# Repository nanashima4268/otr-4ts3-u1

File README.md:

# OTR-4TS3-U1

Open Tuner Receiver。地デジ、BS/110 度 CS、CATV を 4 系統同時に受信できるボードで、ISDB-S3（BS4K）の復調チップへの載せ替えにも対応する。

- ホストとの接続：USB3（FX3）。FPGA（iCE40HX4K-TQ144、中身は HX8K と同じダイ）で 4 系統の TS／TLV を 1 本にまとめる
- 形状：PCIe ロープロファイル（PCIe からは電源だけを取る）と外付け箱の両対応
- 暗号の解除（B-CAS、ACAS）の機能は持たない
- ライセンス（`LICENSES/` を参照）
  - `hw/`：CERN-OHL-S-2.0
  - `fpga/` と `host/`：GPL-2.0-only（px4_drv から派生したコードを含むため）
  - `fx3/`：MIT（FX3 SDK のライブラリはソース非公開のため。ファームのバイナリには Cypress の利用規約がかかる）
  - `docs/`：CERN-OHL-S-2.0（ハードウェア設計資料の一部として）

## ドキュメント

- [docs/research.md](docs/research.md)：事前調査（参照ボードの解析、チップ、先行例、RF・電源・製造の定石、法的な線引き、リスク）
- [docs/decisions.md](docs/decisions.md)：決定事項ログ
- [docs/architecture.md](docs/architecture.md)：ブロック図、電源ツリー、電力見積もり
- [docs/measurement-procedure.md](docs/measurement-procedure.md)：参照ボードの実測手順
- [docs/bom-candidates.md](docs/bom-candidates.md)：部品候補表
- [docs/preverification-plan.md](docs/preverification-plan.md)：ファームウェアとソフトウェアの先行検証計画
- [docs/reference/photos/](docs/reference/photos/)：参照ボード DTV02A-4TS-P の写真

## 状態

設計前の調査段階。回路図はまだない。参照ボードの実測（docs/measurement-procedure.md）を進めている。

## 注意

- 本プロジェクトは、B-CAS や ACAS で暗号化された放送を復号する機能を提供しない。また、提供する予定もない。
- Sony の CXD2856ER と CXD2858ER の情報は、公開されている GPL のドライバと、購入した製品の実測から得たもの。Sony とは関係がなく、NDA に基づく情報は含まない。

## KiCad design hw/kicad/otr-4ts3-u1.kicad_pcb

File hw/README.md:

# hw

KiCad project for the OTR-4TS3-U1 board (4-layer, JLC04161H-7628 stackup). License: CERN-OHL-S-2.0 (see ../LICENSES).
See ../docs/architecture.md.

## Generated design (D-51)

The schematic is generated, not drawn: `hw/gen/design.py` describes the circuit in Python, and `hw/gen/schgen.py` writes `hw/kicad/*.kicad_sch`. Every pin connects through a global label at its end point, so the netlist is exactly the description.

```sh
python3 hw/gen/symbols.py   # project symbols -> hw/lib/otr.kicad_sym (FX3 from the datasheet ball map)
python3 hw/gen/design.py    # schematic + verification
```

Verification:
- The netlist that KiCad exports (`kicad-cli sch export netlist`) must equal the description.
- Every pin of every symbol must be assigned (`NC` for unused pins).
- Pins that the library draws stacked must share a net.
- Library no-connect pins must be `NC`.
- ERC runs (`kicad-cli sch erc`).

Phase 1 covers everything except the Sony receiver core. The receiver core waits for the reference-board measurement and the photo survey, because the CXD2856ER/CXD2858ER pinouts are not public.

Status (2026-11-01):
- Sheets done:
  - FX3
  - FPGA (also generates `fpga/syn/otr_top.pcf`)
  - Power: PCIe/DC 12 V OR, TPS54302 3.3 V, LDOs, `+VIO_TS` selection
  - USB: Type-C via HD3SS3220, or the internal header
  - Control: TCA9546A, LNA bypass inverter
  - RF front end: F jacks, LNA with bypass, 4-way splitters
- The netlist equals the description, and ERC reports 0 errors.
- The 32 remaining ERC warnings are labels for the receiver interface: TS*, RF_T*/RF_S*, CH*_PWR_EN/RST_N. They wait for the receiver sheet (Sony parts, after the measurement).
- Project symbols and footprints are generated by `hw/gen/symbols.py`:
  - CYUSB3014 from the ball map
  - HD3SS3220
  - The DS803FPR0016 F-jack footprint from the maker's recommended layout

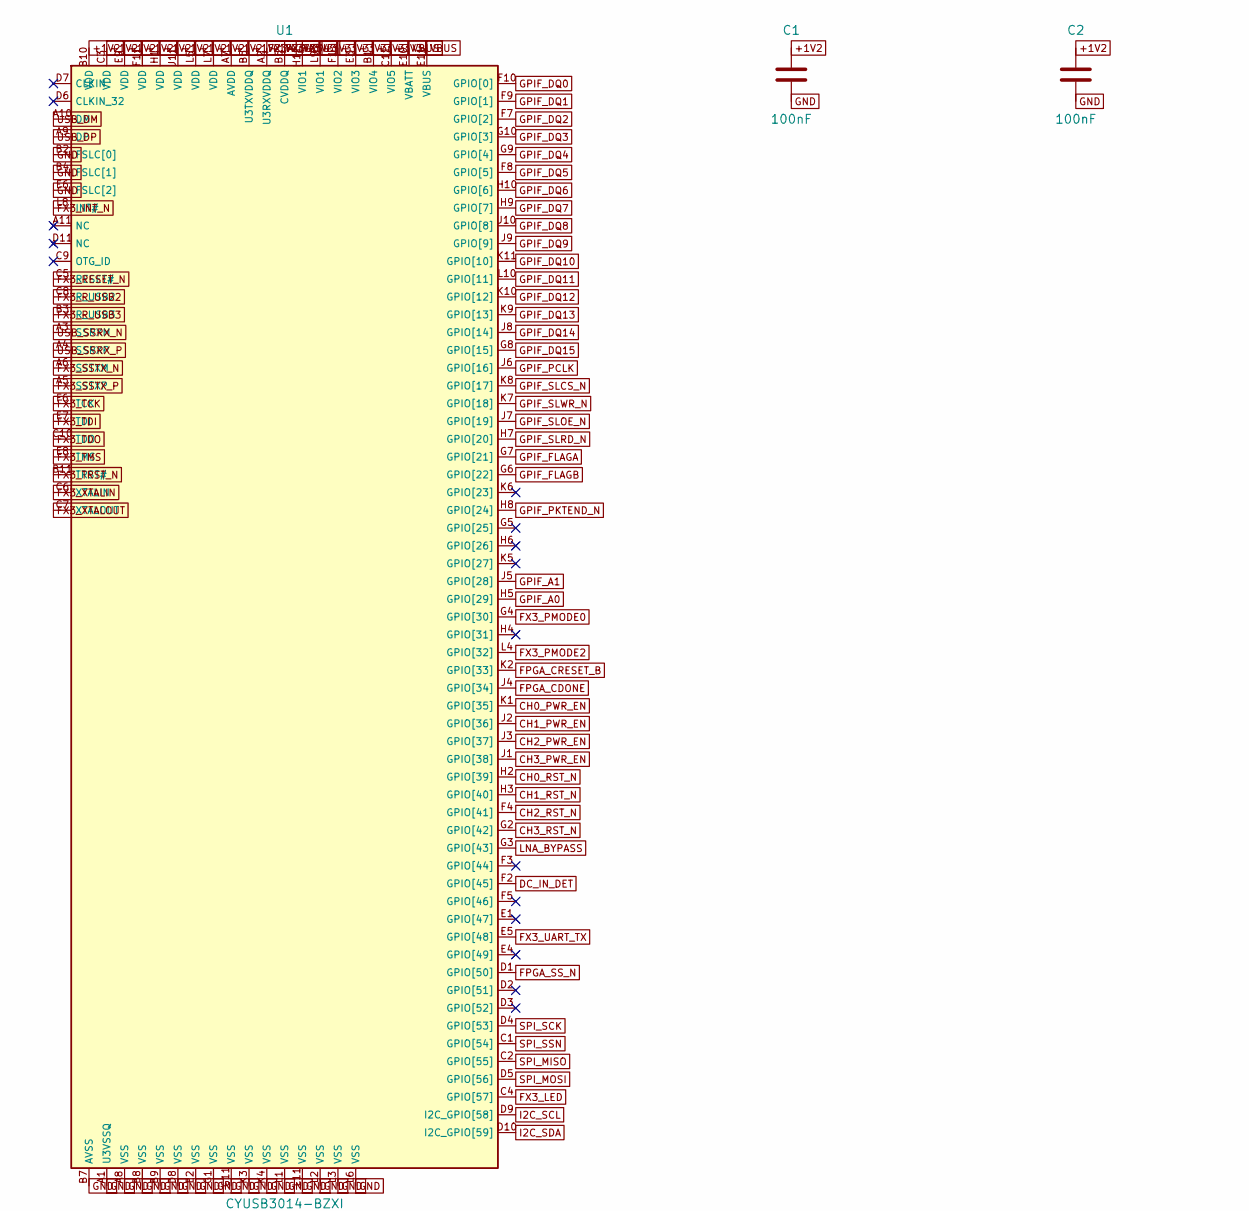
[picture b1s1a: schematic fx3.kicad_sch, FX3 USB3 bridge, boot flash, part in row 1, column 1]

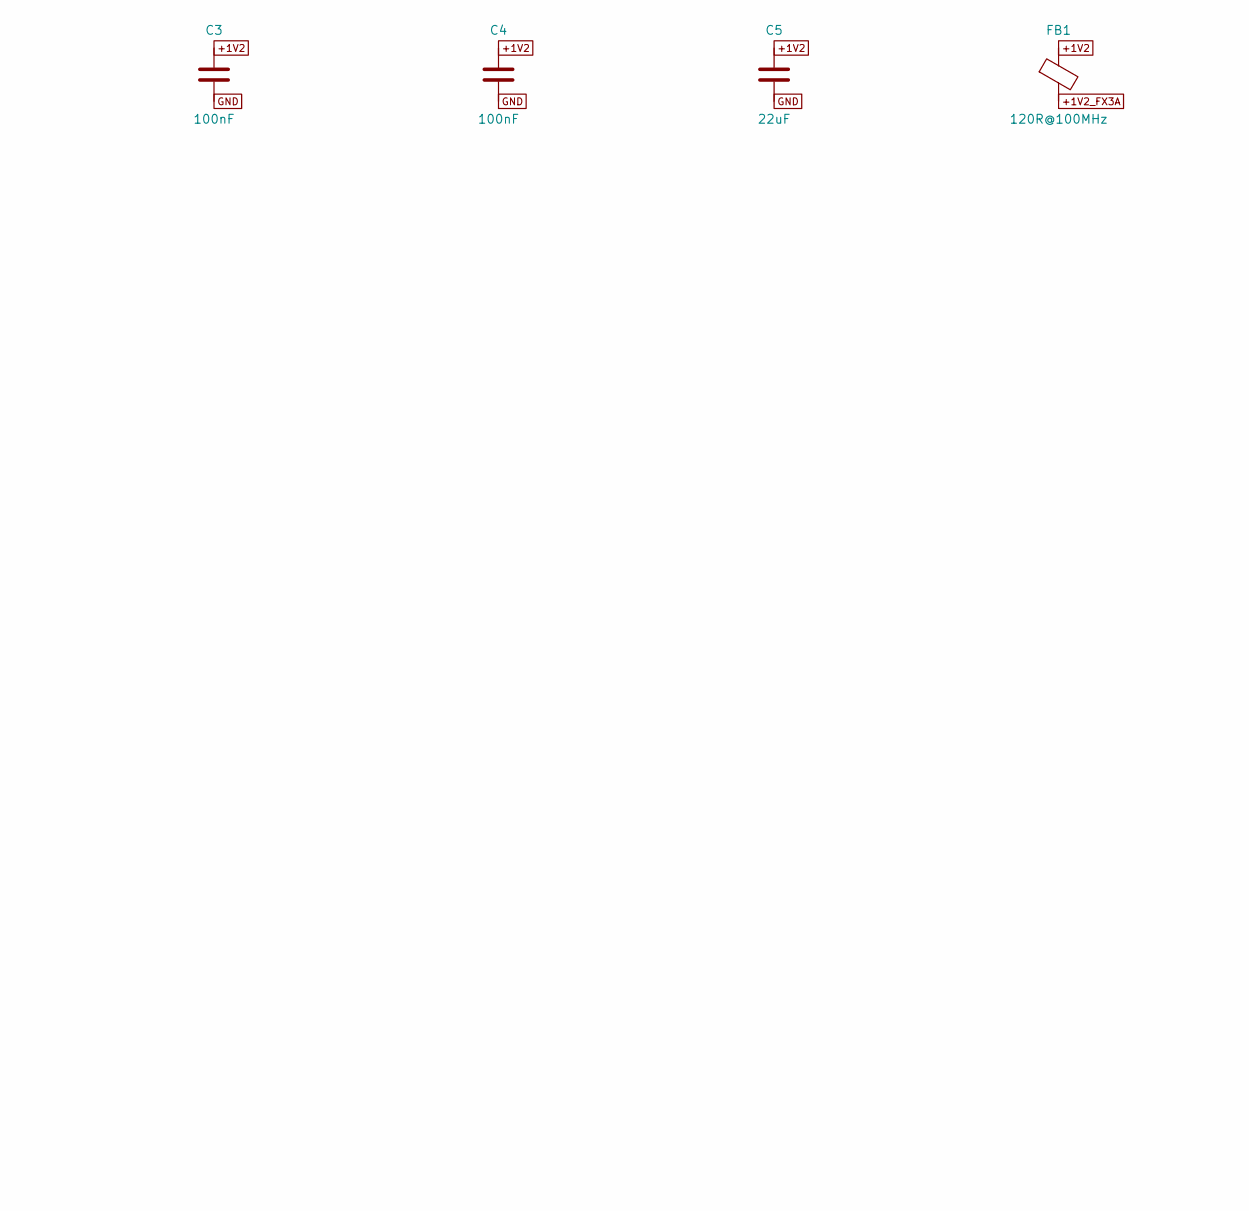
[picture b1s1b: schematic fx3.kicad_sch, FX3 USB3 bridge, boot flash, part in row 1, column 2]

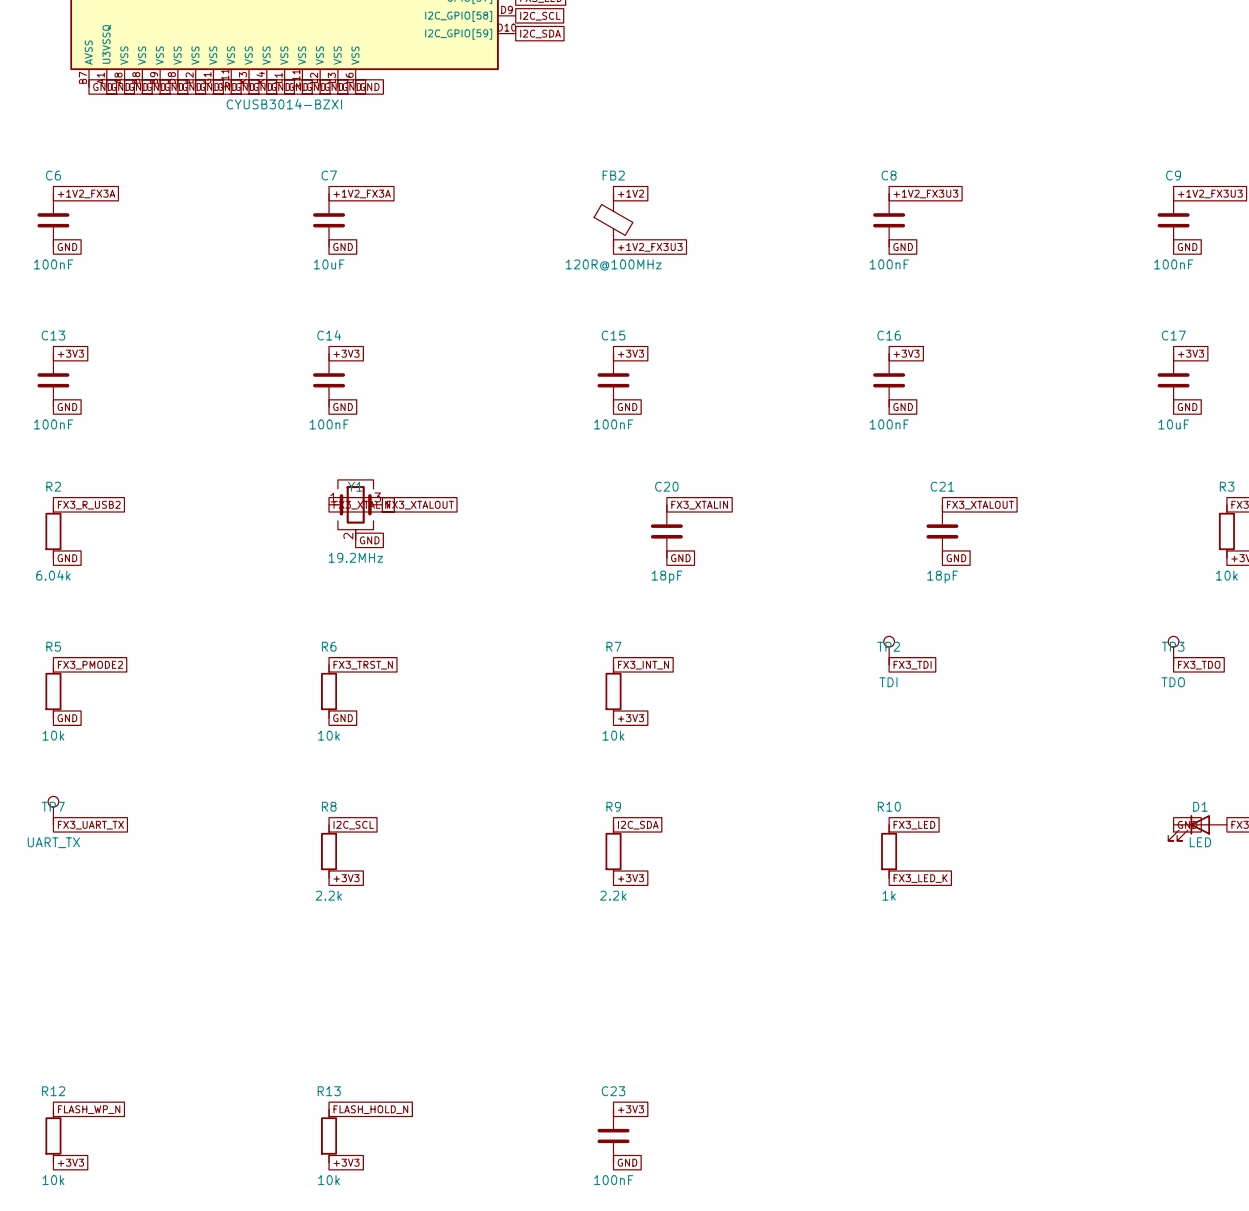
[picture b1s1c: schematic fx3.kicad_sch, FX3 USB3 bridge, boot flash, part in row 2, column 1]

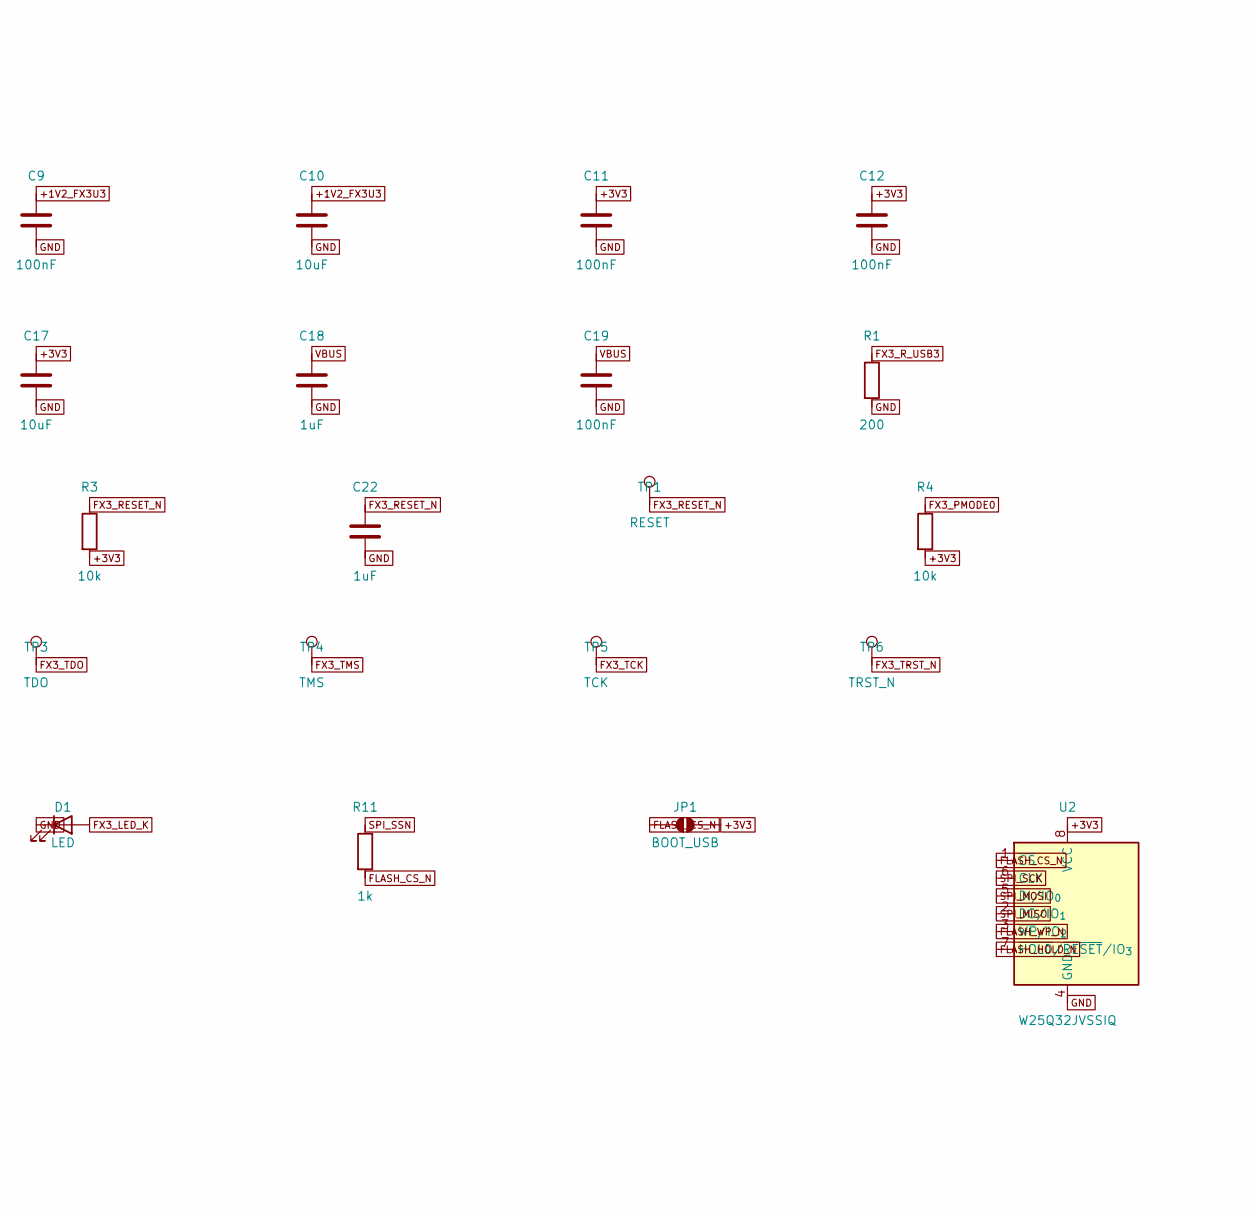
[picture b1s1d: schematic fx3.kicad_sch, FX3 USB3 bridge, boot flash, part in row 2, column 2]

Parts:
C1, C2, C3, C4, C6, C8, C9, C11, C12, C13, C14, C15, C16, C19, C23: 100nF; C_0402_1005Metric; LCSC C1525
C5: 22uF; C_0805_2012Metric; LCSC C45783
C7, C10, C17: 10uF; C_0603_1608Metric; LCSC C19702
C18, C22: 1uF; C_0402_1005Metric; LCSC C52923
C20, C21: 18pF; C_0402_1005Metric; LCSC C1549
D1: LED; LED_0603_1608Metric; LCSC C2286
FB1, FB2: 120R@100MHz; L_0603_1608Metric; LCSC C14709
JP1: BOOT_USB; SolderJumper-2_P1.3mm_Open_RoundedPad1.0x1.5mm
R1: 200; R_0402_1005Metric; LCSC C25087
R2: 6.04k; R_0402_1005Metric; LCSC C97819
R3, R4, R5, R6, R7, R12, R13: 10k; R_0402_1005Metric; LCSC C25744
R8, R9: 2.2k; R_0402_1005Metric; LCSC C25879
R10, R11: 1k; R_0402_1005Metric; LCSC C11702
TP1: RESET; TestPoint_Pad_D1.0mm
TP2: TDI; TestPoint_Pad_D1.0mm
TP3: TDO; TestPoint_Pad_D1.0mm
TP4: TMS; TestPoint_Pad_D1.0mm
TP5: TCK; TestPoint_Pad_D1.0mm
TP6: TRST_N; TestPoint_Pad_D1.0mm
TP7: UART_TX; TestPoint_Pad_D1.0mm
U1: CYUSB3014-BZXI; TFBGA-121_10x10mm_Layout11x11_P0.8mm; LCSC C57294
U2: W25Q32JVSSIQ; SOIC-8_5.3x5.3mm_P1.27mm; LCSC C179173
Y1: 19.2MHz; Crystal_SMD_3225-4Pin_3.2x2.5mm; LCSC C358650

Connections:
+1V2: C1.1, C2.1, C3.1, C4.1, C5.1, FB1.1, FB2.1, U1.B10 (VDD), U1.C3 (VDD), U1.E9 (VDD), U1.F11 (VDD), U1.H1 (VDD), U1.J11 (VDD), U1.L5 (VDD), U1.L7 (VDD); also elsewhere on the board
+1V2_FX3A: C6.1, C7.1, FB1.2, U1.A7 (AVDD)
+1V2_FX3U3: C8.1, C9.1, C10.1, FB2.2, U1.A2 (U3RXVDDQ), U1.B5 (U3TXVDDQ)
+3V3: C11.1, C12.1, C13.1, C14.1, C15.1, C16.1, C17.1, C23.1, JP1.2 (B), R3.2, R4.2, R7.2, R8.2, R9.2, R12.2, R13.2, U1.B1 (VIO4), U1.B6 (CVDDQ), U1.C11 (VIO5), U1.E3 (VIO3), U1.F1 (VIO2), U1.H11 (VIO1), U1.L9 (VIO1), U2.8 (VCC); also elsewhere on the board
CH0_PWR_EN: U1.K1 (GPIO[35])
CH0_RST_N: U1.H2 (GPIO[39])
CH1_PWR_EN: U1.J2 (GPIO[36])
CH1_RST_N: U1.H3 (GPIO[40])
CH2_PWR_EN: U1.J3 (GPIO[37])
CH2_RST_N: U1.F4 (GPIO[41])
CH3_PWR_EN: U1.J1 (GPIO[38])
CH3_RST_N: U1.G2 (GPIO[42])
DC_IN_DET: U1.F2 (GPIO[45]); also elsewhere on the board
FLASH_CS_N: JP1.1 (A), R11.2, U2.1 (~CS)
FLASH_HOLD_N: R13.1, U2.7 (~HOLD/~RESET/IO_{3})
FLASH_WP_N: R12.1, U2.3 (~WP/IO_{2})
FPGA_CDONE: U1.J4 (GPIO[34]); also elsewhere on the board
FPGA_CRESET_B: U1.K2 (GPIO[33]); also elsewhere on the board
FPGA_SS_N: U1.D1 (GPIO[50]); also elsewhere on the board
FX3_INT_N: R7.1, U1.L8 (INT#)
FX3_LED: R10.1, U1.C4 (GPIO[57])
FX3_LED_K: D1.2 (A), R10.2
FX3_PMODE0: R4.1, U1.G4 (GPIO[30])
FX3_PMODE2: R5.1, U1.L4 (GPIO[32])
FX3_RESET_N: C22.1, R3.1, TP1.1, U1.C5 (RESET#)
FX3_R_USB2: R2.1, U1.C8 (R_USB2)
FX3_R_USB3: R1.1, U1.B3 (R_USB3)
FX3_SSTX_N: U1.A6 (SSTXM); also elsewhere on the board
FX3_SSTX_P: U1.A5 (SSTXP); also elsewhere on the board
FX3_TCK: TP5.1, U1.F6 (TCK)
FX3_TDI: TP2.1, U1.E7 (TDI)
FX3_TDO: TP3.1, U1.C10 (TDO)
FX3_TMS: TP4.1, U1.E8 (TMS)
FX3_TRST_N: R6.1, TP6.1, U1.B11 (TRST#)
FX3_UART_TX: TP7.1, U1.E5 (GPIO[48])
FX3_XTALIN: C20.1, U1.C6 (XTALIN), Y1.1
FX3_XTALOUT: C21.1, U1.C7 (XTALOUT), Y1.3
GND: C1.2, C2.2, C3.2, C4.2, C5.2, C6.2, C7.2, C8.2, C9.2, C10.2, C11.2, C12.2, C13.2, C14.2, C15.2, C16.2, C17.2, C18.2, C19.2, C20.2, C21.2, C22.2, C23.2, D1.1 (K), R1.2, R2.2, R5.2, R6.2, U1.A1 (U3VSSQ), U1.A8 (VSS), U1.B2 (FSLC[0]), U1.B4 (FSLC[1]), U1.B7 (AVSS), U1.B8 (VSS), U1.B9 (VSS), U1.D8 (VSS), U1.E2 (VSS), U1.E6 (FSLC[2]), U1.G1 (VSS), U1.G11 (VSS), U1.K3 (VSS), U1.K4 (VSS), U1.L1 (VSS), U1.L2 (VSS), U1.L3 (VSS), U1.L6 (VSS), U1.L11 (VSS), U2.4 (GND), Y1.2 (G), Y1.4 (G); also elsewhere on the board
GPIF_A0: U1.H5 (GPIO[29]); also elsewhere on the board
GPIF_A1: U1.J5 (GPIO[28]); also elsewhere on the board
GPIF_DQ0: U1.F10 (GPIO[0]); also elsewhere on the board
GPIF_DQ1: U1.F9 (GPIO[1]); also elsewhere on the board
GPIF_DQ2: U1.F7 (GPIO[2]); also elsewhere on the board
GPIF_DQ3: U1.G10 (GPIO[3]); also elsewhere on the board
GPIF_DQ4: U1.G9 (GPIO[4]); also elsewhere on the board
GPIF_DQ5: U1.F8 (GPIO[5]); also elsewhere on the board
GPIF_DQ6: U1.H10 (GPIO[6]); also elsewhere on the board
GPIF_DQ7: U1.H9 (GPIO[7]); also elsewhere on the board
GPIF_DQ8: U1.J10 (GPIO[8]); also elsewhere on the board
GPIF_DQ9: U1.J9 (GPIO[9]); also elsewhere on the board
GPIF_DQ10: U1.K11 (GPIO[10]); also elsewhere on the board
GPIF_DQ11: U1.L10 (GPIO[11]); also elsewhere on the board
GPIF_DQ12: U1.K10 (GPIO[12]); also elsewhere on the board
GPIF_DQ13: U1.K9 (GPIO[13]); also elsewhere on the board
GPIF_DQ14: U1.J8 (GPIO[14]); also elsewhere on the board
GPIF_DQ15: U1.G8 (GPIO[15]); also elsewhere on the board
GPIF_FLAGA: U1.G7 (GPIO[21]); also elsewhere on the board
GPIF_FLAGB: U1.G6 (GPIO[22]); also elsewhere on the board
GPIF_PCLK: U1.J6 (GPIO[16]); also elsewhere on the board
GPIF_PKTEND_N: U1.H8 (GPIO[24]); also elsewhere on the board
GPIF_SLCS_N: U1.K8 (GPIO[17]); also elsewhere on the board
GPIF_SLOE_N: U1.J7 (GPIO[19]); also elsewhere on the board
GPIF_SLRD_N: U1.H7 (GPIO[20]); also elsewhere on the board
GPIF_SLWR_N: U1.K7 (GPIO[18]); also elsewhere on the board
I2C_SCL: R8.1, U1.D9 (I2C_GPIO[58]); also elsewhere on the board
I2C_SDA: R9.1, U1.D10 (I2C_GPIO[59]); also elsewhere on the board
LNA_BYPASS: U1.G3 (GPIO[43]); also elsewhere on the board
SPI_MISO: U1.C2 (GPIO[55]), U2.2 (DO/IO_{1}); also elsewhere on the board
SPI_MOSI: U1.D5 (GPIO[56]), U2.5 (DI/IO_{0}); also elsewhere on the board
SPI_SCK: U1.D4 (GPIO[53]), U2.6 (CLK); also elsewhere on the board
SPI_SSN: R11.1, U1.C1 (GPIO[54])
USB_DM: U1.A10 (DM); also elsewhere on the board
USB_DP: U1.A9 (DP); also elsewhere on the board
USB_SSRX_N: U1.A3 (SSRXM); also elsewhere on the board
USB_SSRX_P: U1.A4 (SSRXP); also elsewhere on the board
VBUS: C18.1, C19.1, U1.E10 (VBATT), U1.E11 (VBUS); also elsewhere on the board

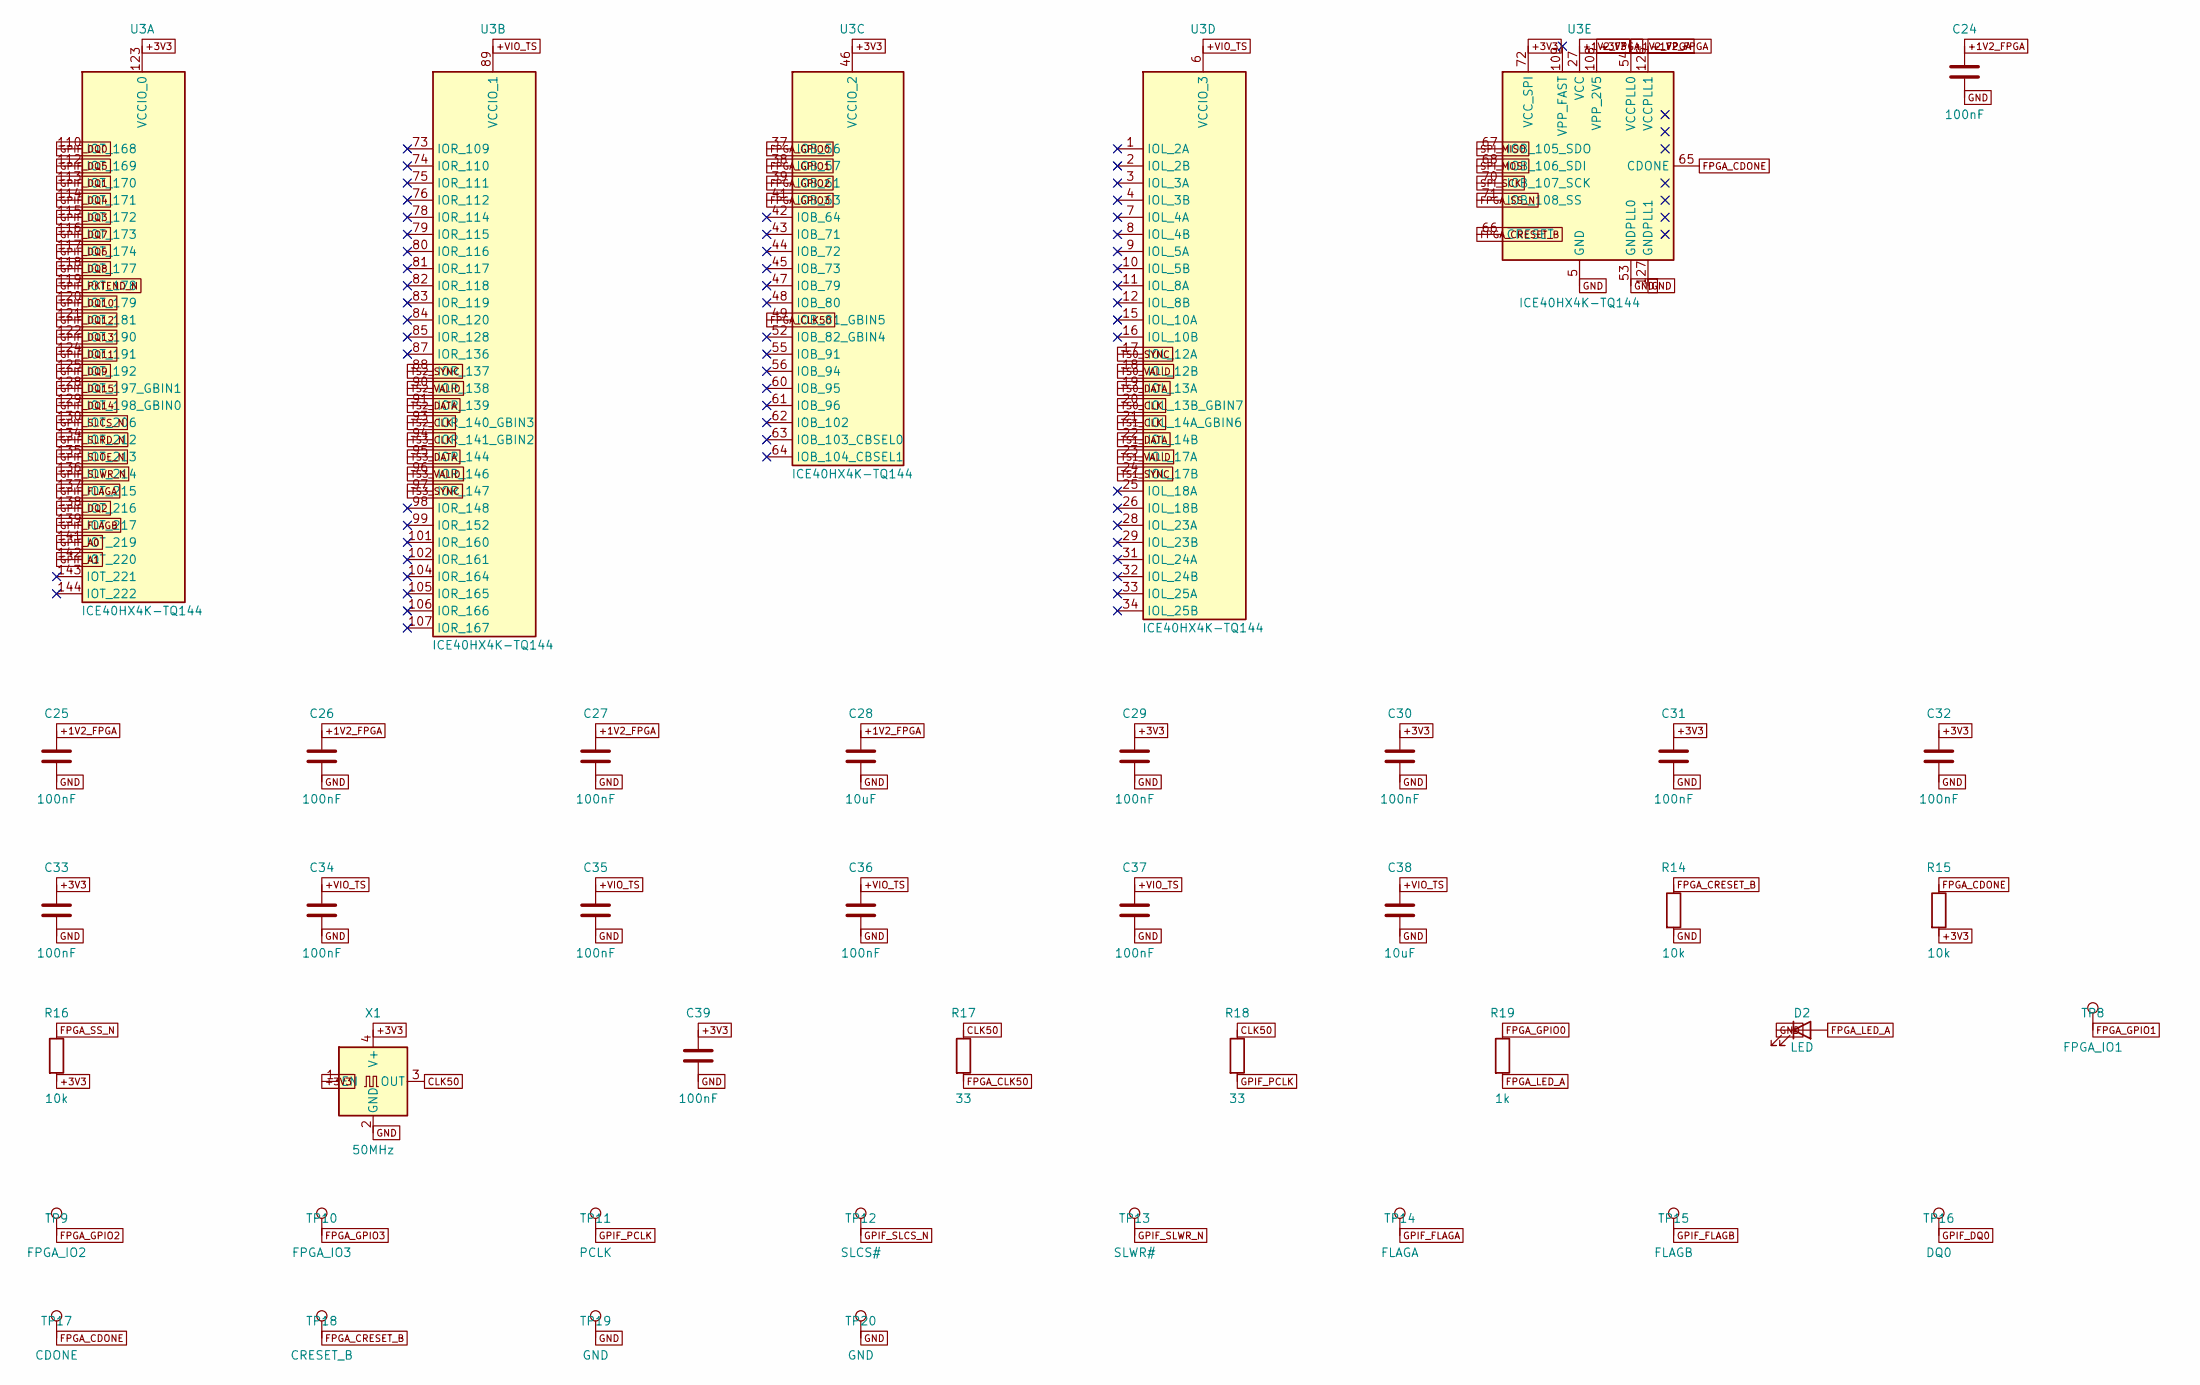
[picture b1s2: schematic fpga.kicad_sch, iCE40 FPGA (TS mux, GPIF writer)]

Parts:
C24, C25, C26, C27, C29, C30, C31, C32, C33, C34, C35, C36, C37, C39: 100nF; C_0402_1005Metric; LCSC C1525
C28, C38: 10uF; C_0603_1608Metric; LCSC C19702
D2: LED; LED_0603_1608Metric; LCSC C2286
R14, R15, R16: 10k; R_0402_1005Metric; LCSC C25744
R17, R18: 33; R_0402_1005Metric; LCSC C25105
R19: 1k; R_0402_1005Metric; LCSC C11702
TP8: FPGA_IO1; TestPoint_Pad_D1.0mm
TP9: FPGA_IO2; TestPoint_Pad_D1.0mm
TP10: FPGA_IO3; TestPoint_Pad_D1.0mm
TP11: PCLK; TestPoint_Pad_D1.0mm
TP12: SLCS#; TestPoint_Pad_D1.0mm
TP13: SLWR#; TestPoint_Pad_D1.0mm
TP14: FLAGA; TestPoint_Pad_D1.0mm
TP15: FLAGB; TestPoint_Pad_D1.0mm
TP16: DQ0; TestPoint_Pad_D1.0mm
TP17: CDONE; TestPoint_Pad_D1.0mm
TP18: CRESET_B; TestPoint_Pad_D1.0mm
TP19, TP20: GND; TestPoint_Pad_D1.0mm
U3: ICE40HX4K-TQ144; TQFP-144_20x20mm_P0.5mm; LCSC C1521989
X1: 50MHz; Oscillator_SMD_EuroQuartz_XO32-4Pin_3.2x2.5mm; LCSC C5203552

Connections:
+1V2_FPGA: C24.1, C25.1, C26.1, C27.1, C28.1, U3.27 (VCC), U3.40 (VCC), U3.54 (VCCPLL0), U3.92 (VCC), U3.111 (VCC), U3.126 (VCCPLL1); also elsewhere on the board
+3V3: C29.1, C30.1, C31.1, C32.1, C33.1, C39.1, R15.2, R16.2, U3.46 (VCCIO_2), U3.57 (VCCIO_2), U3.72 (VCC_SPI), U3.108 (VPP_2V5), U3.123 (VCCIO_0), U3.131 (VCCIO_0), X1.1 (EN), X1.4 (V+); also elsewhere on the board
+VIO_TS: C34.1, C35.1, C36.1, C37.1, C38.1, U3.6 (VCCIO_3), U3.30 (VCCIO_3), U3.89 (VCCIO_1), U3.100 (VCCIO_1); also elsewhere on the board
CLK50: R17.1, R18.1, X1.3 (OUT)
FPGA_CDONE: R15.1, TP17.1, U3.65 (CDONE); also elsewhere on the board
FPGA_CLK50: R17.2, U3.49 (IOB_81_GBIN5)
FPGA_CRESET_B: R14.1, TP18.1, U3.66 (~CRESET); also elsewhere on the board
FPGA_GPIO0: R19.1, U3.37 (IOB_56)
FPGA_GPIO1: TP8.1, U3.38 (IOB_57)
FPGA_GPIO2: TP9.1, U3.39 (IOB_61)
FPGA_GPIO3: TP10.1, U3.41 (IOB_63)
FPGA_LED_A: D2.2 (A), R19.2
FPGA_SS_N: R16.1, U3.71 (IOB_108_SS); also elsewhere on the board
GND: C24.2, C25.2, C26.2, C27.2, C28.2, C29.2, C30.2, C31.2, C32.2, C33.2, C34.2, C35.2, C36.2, C37.2, C38.2, C39.2, D2.1 (K), R14.2, TP19.1, TP20.1, U3.5 (GND), U3.13 (GND), U3.14 (GND), U3.53 (GNDPLL0), U3.59 (GND), U3.69 (GND), U3.86 (GND), U3.103 (GND), U3.127 (GNDPLL1), U3.132 (GND), U3.140 (GND), X1.2 (GND); also elsewhere on the board
GPIF_A0: U3.141 (IOT_219); also elsewhere on the board
GPIF_A1: U3.142 (IOT_220); also elsewhere on the board
GPIF_DQ0: TP16.1, U3.110 (IOT_168); also elsewhere on the board
GPIF_DQ1: U3.113 (IOT_170); also elsewhere on the board
GPIF_DQ2: U3.138 (IOT_216); also elsewhere on the board
GPIF_DQ3: U3.115 (IOT_172); also elsewhere on the board
GPIF_DQ4: U3.114 (IOT_171); also elsewhere on the board
GPIF_DQ5: U3.112 (IOT_169); also elsewhere on the board
GPIF_DQ6: U3.117 (IOT_174); also elsewhere on the board
GPIF_DQ7: U3.116 (IOT_173); also elsewhere on the board
GPIF_DQ8: U3.118 (IOT_177); also elsewhere on the board
GPIF_DQ9: U3.125 (IOT_192); also elsewhere on the board
GPIF_DQ10: U3.120 (IOT_179); also elsewhere on the board
GPIF_DQ11: U3.124 (IOT_191); also elsewhere on the board
GPIF_DQ12: U3.121 (IOT_181); also elsewhere on the board
GPIF_DQ13: U3.122 (IOT_190); also elsewhere on the board
GPIF_DQ14: U3.129 (IOT_198_GBIN0); also elsewhere on the board
GPIF_DQ15: U3.128 (IOT_197_GBIN1); also elsewhere on the board
GPIF_FLAGA: TP14.1, U3.137 (IOT_215); also elsewhere on the board
GPIF_FLAGB: TP15.1, U3.139 (IOT_217); also elsewhere on the board
GPIF_PCLK: R18.2, TP11.1; also elsewhere on the board
GPIF_PKTEND_N: U3.119 (IOT_178); also elsewhere on the board
GPIF_SLCS_N: TP12.1, U3.130 (IOT_206); also elsewhere on the board
GPIF_SLOE_N: U3.135 (IOT_213); also elsewhere on the board
GPIF_SLRD_N: U3.134 (IOT_212); also elsewhere on the board
GPIF_SLWR_N: TP13.1, U3.136 (IOT_214); also elsewhere on the board
SPI_MISO: U3.67 (IOB_105_SDO); also elsewhere on the board
SPI_MOSI: U3.68 (IOB_106_SDI); also elsewhere on the board
SPI_SCK: U3.70 (IOB_107_SCK); also elsewhere on the board
TS0_CLK: U3.20 (IOL_13B_GBIN7)
TS0_DATA: U3.19 (IOL_13A)
TS0_SYNC: U3.17 (IOL_12A)
TS0_VALID: U3.18 (IOL_12B)
TS1_CLK: U3.21 (IOL_14A_GBIN6)
TS1_DATA: U3.22 (IOL_14B)
TS1_SYNC: U3.24 (IOL_17B)
TS1_VALID: U3.23 (IOL_17A)
TS2_CLK: U3.93 (IOR_140_GBIN3)
TS2_DATA: U3.91 (IOR_139)
TS2_SYNC: U3.88 (IOR_137)
TS2_VALID: U3.90 (IOR_138)
TS3_CLK: U3.94 (IOR_141_GBIN2)
TS3_DATA: U3.95 (IOR_144)
TS3_SYNC: U3.97 (IOR_147)
TS3_VALID: U3.96 (IOR_146)

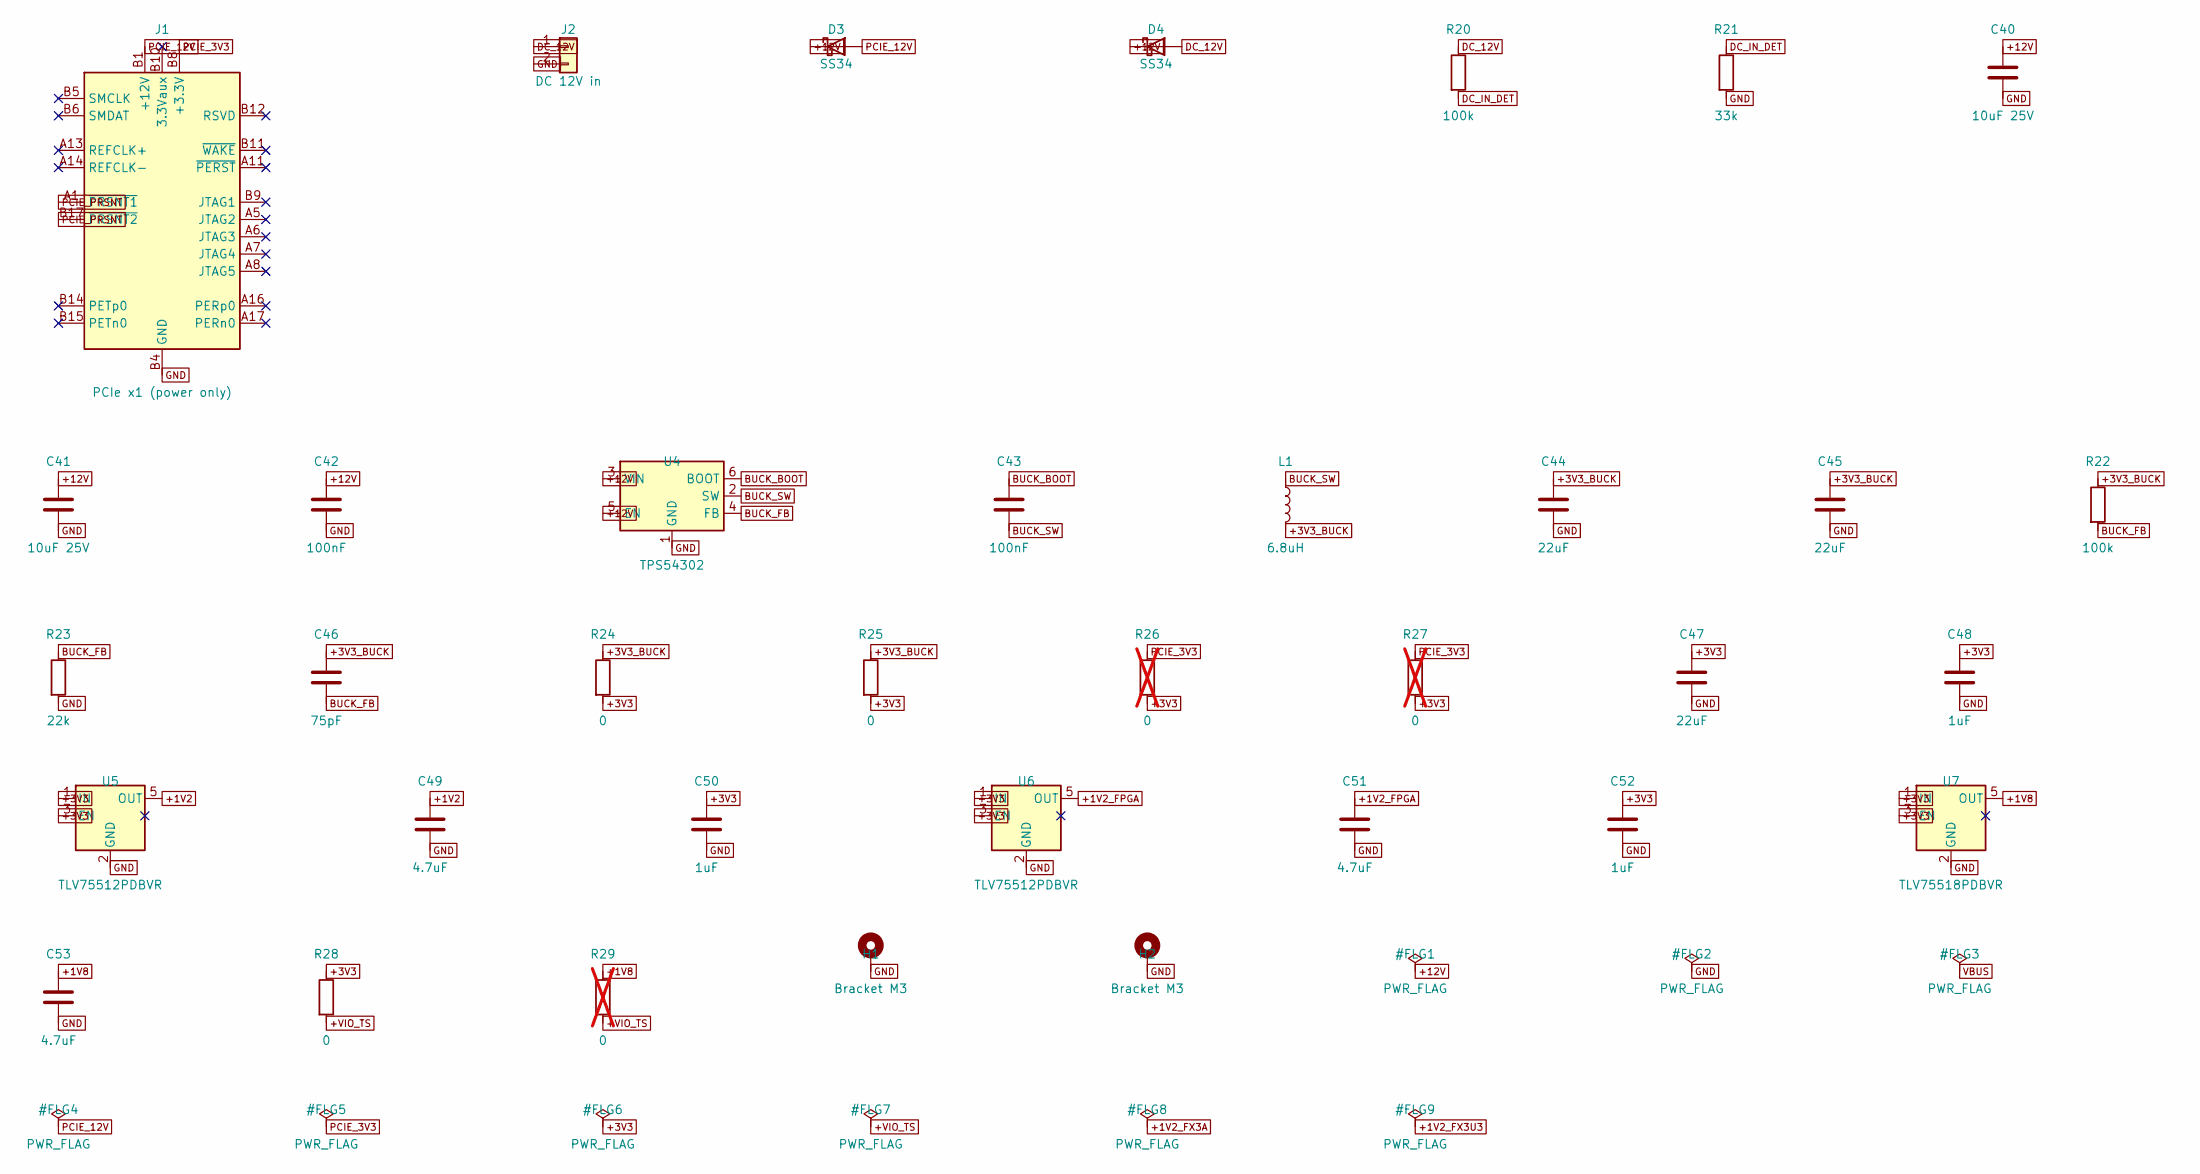
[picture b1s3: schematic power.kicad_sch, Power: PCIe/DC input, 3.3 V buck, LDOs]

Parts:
C40, C41: 10uF 25V; C_0805_2012Metric; LCSC C15850
C42, C43: 100nF; C_0402_1005Metric; LCSC C1525
C44, C45, C47: 22uF; C_0805_2012Metric; LCSC C45783
C46: 75pF; C_0402_1005Metric; LCSC C107010
C48, C50, C52: 1uF; C_0402_1005Metric; LCSC C52923
C49, C51, C53: 4.7uF; C_0402_1005Metric; LCSC C23733
D3, D4: SS34; D_SMA; LCSC C8678
H1, H2: Bracket M3; MountingHole_3.2mm_M3_Pad_Via
J1: PCIe x1 (power only); BUS_PCIexpress_x1
J2: DC 12V in; JST_XH_B2B-XH-A_1x02_P2.50mm_Vertical; LCSC C158012
L1: 6.8uH; L_6.3x6.3_H3; LCSC C354631
R20, R22: 100k; R_0402_1005Metric; LCSC C25741
R21: 33k; R_0402_1005Metric; LCSC C25779
R23: 22k; R_0402_1005Metric; LCSC C25768
R24, R25: 0; R_1206_3216Metric; LCSC C17888
R26, R27: 0; R_1206_3216Metric; LCSC C17888; not fitted
R28: 0; R_0402_1005Metric; LCSC C17168
R29: 0; R_0402_1005Metric; LCSC C17168; not fitted
U4: TPS54302; SOT-23-6; LCSC C311983
U5, U6: TLV75512PDBVR; SOT-23-5; LCSC C2877864
U7: TLV75518PDBVR; SOT-23-5; LCSC C2877863

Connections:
+1V2: C49.1, U5.5 (OUT); also elsewhere on the board
+1V2_FPGA: C51.1, U6.5 (OUT); also elsewhere on the board
+1V8: C53.1, R29.1, U7.5 (OUT)
+3V3: C47.1, C48.1, C50.1, C52.1, R24.2, R25.2, R26.2, R27.2, R28.1, U5.1 (IN), U5.3 (EN), U6.1 (IN), U6.3 (EN), U7.1 (IN), U7.3 (EN); also elsewhere on the board
+3V3_BUCK: C44.1, C45.1, C46.1, L1.2, R22.1, R24.1, R25.1
+12V: C40.1, C41.1, C42.1, D3.1 (K), D4.1 (K), U4.3 (VIN), U4.5 (EN)
+VIO_TS: R28.2, R29.2; also elsewhere on the board
BUCK_BOOT: C43.1, U4.6 (BOOT)
BUCK_FB: C46.2, R22.2, R23.1, U4.4 (FB)
BUCK_SW: C43.2, L1.1, U4.2 (SW)
DC_12V: D4.2 (A), J2.1, R20.1
DC_IN_DET: R20.2, R21.1; also elsewhere on the board
GND: C40.2, C41.2, C42.2, C44.2, C45.2, C47.2, C48.2, C49.2, C50.2, C51.2, C52.2, C53.2, H1.1, H2.1, J1.A4 (GND), J1.A12 (GND), J1.A15 (GND), J1.A18 (GND), J1.B4 (GND), J1.B7 (GND), J1.B13 (GND), J1.B16 (GND), J1.B18 (GND), J2.2, R21.2, R23.2, U4.1 (GND), U5.2 (GND), U6.2 (GND), U7.2 (GND); also elsewhere on the board
PCIE_3V3: J1.A9 (+3.3V), J1.A10 (+3.3V), J1.B8 (+3.3V), R26.1, R27.1
PCIE_12V: D3.2 (A), J1.A2 (+12V), J1.A3 (+12V), J1.B1 (+12V), J1.B2 (+12V), J1.B3 (+12V)
PCIE_PRSNT: J1.A1 (~PRSNT1), J1.B17 (~PRSNT2)

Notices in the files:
hw/gen/design.py:
SPDX-License-Identifier: CERN-OHL-S-2.0
